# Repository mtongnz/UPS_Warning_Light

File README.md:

# UPS_Warning_Light
Flashing red light when UPS loses power

Instructable: https://www.instructables.com/id/UPS-Warning-Lights/

Demo video: https://youtu.be/_w6m1b8DcVI

PCB Construction & Flashing video here:  https://youtu.be/69Z9agwIDKo

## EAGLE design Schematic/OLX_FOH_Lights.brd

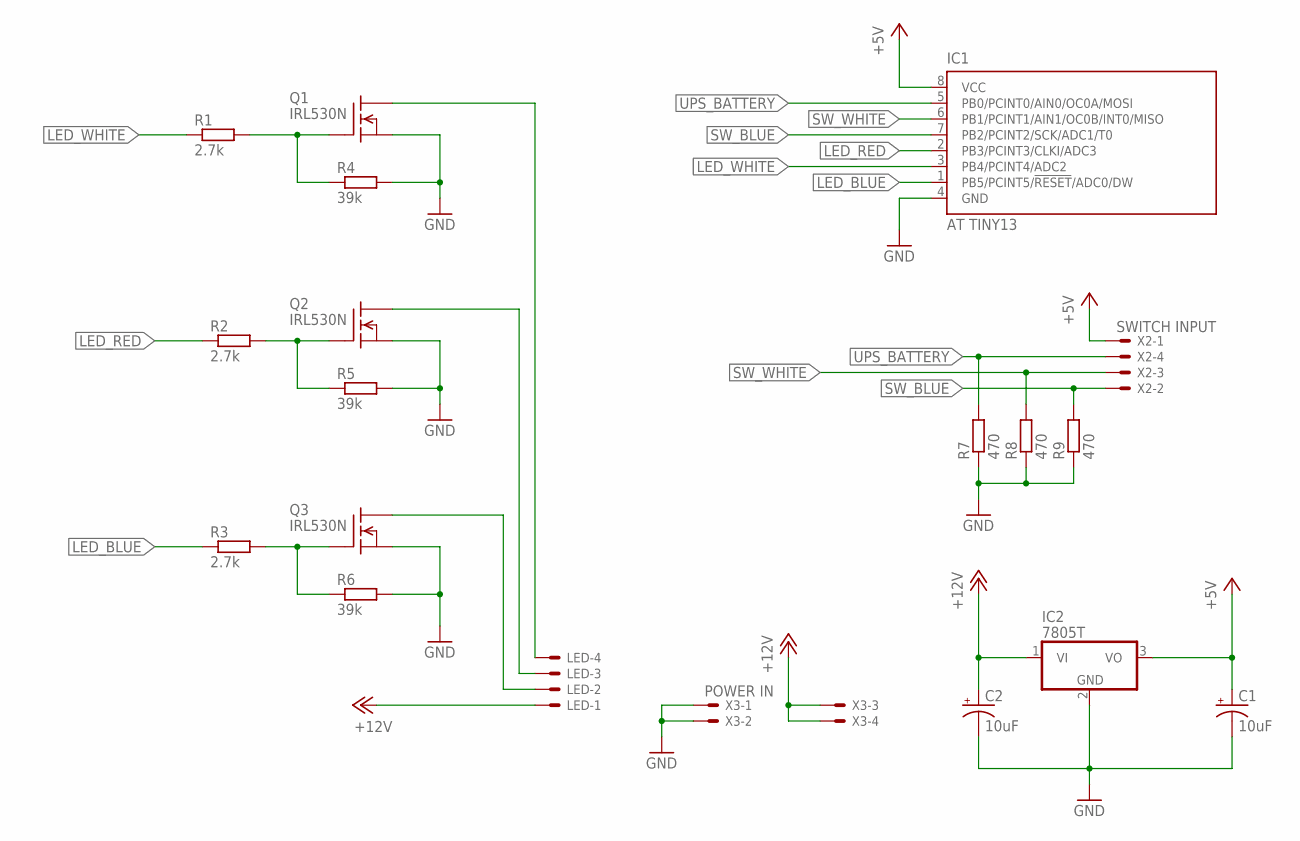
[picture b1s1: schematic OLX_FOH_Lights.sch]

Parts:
C1, C2: 10uF; TT2D4
IC1: AT TINY13; DIL08
IC2: 7805T; TO220H
LED: LED OUTPUT; 22-23-2041
Q1, Q2, Q3: IRL530N; TO220
R1, R2, R3: 2.7k; 0411/12
R4, R5, R6: 39k; 0411/12
R7, R8, R9: 470; 0411/12
X2: SWITCH INPUT; 22-23-2041
X3: POWER IN; 22-23-2041

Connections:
+5V: C1.+, IC1.8 (VCC), IC2.3 (VO), X2.1
+12V: C2.+, IC2.1 (VI), LED.1, X3.3, X3.4
GND: C1.-, C2.-, IC1.4 (GND), IC2.2 (GND), Q1.3 (S), Q2.3 (S), Q3.3 (S), R4.2, R5.2, R6.2, R7.1, R8.1, R9.1, X3.1, X3.2
LED_BLUE: IC1.1 (PB5/PCINT5/!RESET!/ADC0/DW), R3.1
LED_RED: IC1.2 (PB3/PCINT3/CLKI/ADC3), R2.1
LED_WHITE: IC1.3 (PB4/PCINT4/ADC2), R1.1
unnamed: Q1.1 (G), R1.2, R4.1
unnamed: LED.4, Q1.2 (D)
unnamed: LED.3, Q2.2 (D)
unnamed: Q3.1 (G), R3.2, R6.1
unnamed: LED.2, Q3.2 (D)
unnamed: Q2.1 (G), R2.2, R5.1
SW_BLUE: IC1.7 (PB2/PCINT2/SCK/ADC1/T0), R9.2, X2.2
SW_WHITE: IC1.6 (PB1/PCINT1/AIN1/OC0B/INT0/MISO), R8.2, X2.3
UPS_BATTERY: IC1.5 (PB0/PCINT0/AIN0/OC0A/MOSI), R7.2, X2.4

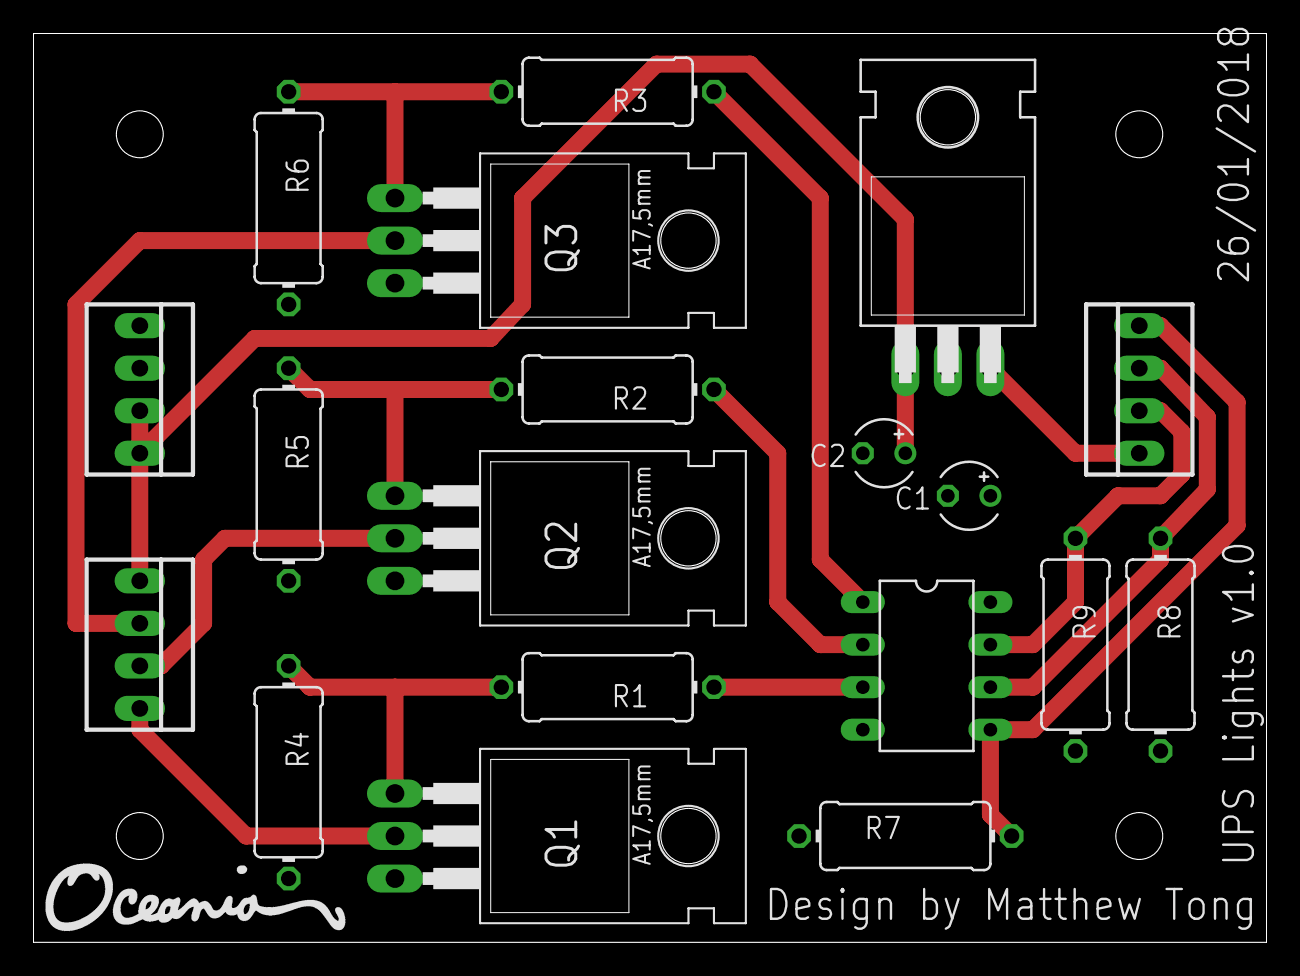
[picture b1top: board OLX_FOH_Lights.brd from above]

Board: 2 copper layers, 73.6 x 54.3 mm, 19 parts (0 on the bottom side), 15 nets.

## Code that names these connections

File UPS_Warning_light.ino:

/*
UPS Warning Light
Copyright (c) 2018, Matthew Tong
https://github.com/mtongnz/UPS_Warning_Light
This program is free software: you can redistribute it and/or modify it under the terms of the GNU General Public
License as published by the Free Software Foundation, either version 3 of the License, or (at your option) any
later version.
This program is distributed in the hope that it will be useful, but WITHOUT ANY WARRANTY; without even the implied
warranty of MERCHANTABILITY or FITNESS FOR A PARTICULAR PURPOSE.  See the GNU General Public License for more details.
You should have received a copy of the GNU General Public License along with this program.
If not, see http://www.gnu.org/licenses/
*/

#define FLASH_RATE 50

#define UPS_BATTERY 0
#define SW_WHITE 1
#define SW_BLUE 2
#define COL_RED 3
#define COL_BLUE 4
#define COL_WHITE 5

enum states {
  OFF,
  WHITE,
  BLUE,
  RED,
  RED_WHITE,
  RED_BLUE
};

uint8_t curState = OFF, prevButton;
bool isBattery = false;
uint16_t counter = 0;


void setup() {
  pinMode(UPS_BATTERY, INPUT);
  pinMode(SW_WHITE, INPUT);
  pinMode(SW_BLUE, INPUT);
  pinMode(COL_RED, OUTPUT);
  pinMode(COL_BLUE, OUTPUT);
  pinMode(COL_WHITE, OUTPUT);

  digitalWrite(COL_RED, HIGH);
  digitalWrite(COL_BLUE, HIGH);
  digitalWrite(COL_WHITE, HIGH);
}


void loop() {

  // Check if we're on battery
  if (digitalRead(UPS_BATTERY) == LOW) {
    delay(5);
    if (digitalRead(UPS_BATTERY) == LOW) {
      if (!isBattery) {
        isBattery = true;
        curState = RED;
        counter = 0;
        prevButton = getButtonValue();
      }
    } else {
      isBattery = false;
      curState = getButtonValue();
    }
  } else {
    isBattery = false;
    curState = getButtonValue();
  }

  switch (curState) {
    case OFF:
      digitalWrite(COL_RED, LOW);
      digitalWrite(COL_BLUE, LOW);
      digitalWrite(COL_WHITE, LOW);
      break;

    case RED_BLUE:
      curState = RED + getButtonValue();
      
      if (++counter < FLASH_RATE) {
        digitalWrite(COL_RED, HIGH);
        digitalWrite(COL_BLUE, HIGH);
        digitalWrite(COL_WHITE, LOW);
        break;
      }
      
    case BLUE:
      digitalWrite(COL_RED, LOW);
      digitalWrite(COL_BLUE, HIGH);
      digitalWrite(COL_WHITE, LOW);
      break;

    case RED_WHITE:
      curState = RED + getButtonValue();
      
      if (++counter < FLASH_RATE) {
        digitalWrite(COL_RED, HIGH);
        digitalWrite(COL_BLUE, LOW);
        digitalWrite(COL_WHITE, HIGH);
        break;
      }
      
    case WHITE:
      digitalWrite(COL_RED, LOW);
      digitalWrite(COL_BLUE, LOW);
      digitalWrite(COL_WHITE, HIGH);
      break;

    case RED:
      if (++counter < FLASH_RATE) {
        digitalWrite(COL_RED, HIGH);
        digitalWrite(COL_BLUE, LOW);
        digitalWrite(COL_WHITE, LOW);
      } else {
        digitalWrite(COL_RED, LOW);
        digitalWrite(COL_BLUE, LOW);
        digitalWrite(COL_WHITE, LOW);
      }
      
      
      if (prevButton == OFF)
        curState = RED + getButtonValue();
      else
        prevButton = getButtonValue();
      
      break;
    
  }
  
  if (counter >= (3 * FLASH_RATE))
    counter = 0;

}


uint8_t getButtonValue(void) {
  if (digitalRead(SW_WHITE) == HIGH && digitalRead(SW_BLUE) == HIGH) {
    delay(5);
    if (digitalRead(SW_WHITE) == HIGH && digitalRead(SW_BLUE) == HIGH)
      return OFF;
  } else if (digitalRead(SW_WHITE) == LOW) {
    delay(5);
    if (digitalRead(SW_WHITE) == LOW)
      return WHITE;
  } else if (digitalRead(SW_BLUE) == LOW) {
    delay(5);
    if (digitalRead(SW_BLUE) == LOW)
      return BLUE;
  } else
    delay(5);

}

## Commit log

2018-04-13 Original commit
2018-04-13 Create a,txt
2018-05-09 Add Youtube link
2018-05-09 Add photo of finished PCB
